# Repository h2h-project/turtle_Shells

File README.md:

# The Hope Turtle Shell
### Our Open Source Printed Circuit Board for the Turtle Control Bottle

The Human2Human project aims to bring hope and humanity to the most hurting and isolated places on the planet — in a way that doesn't trouble the health and happiness of animals, fish and other our fellow creatures. To do so, we've developed the hope turtle: a non-capital, open-source, autonomous marine vehicle that embodies Earthen principles. This repository holds the designs for our "Turtle Shell" printed circuit board.  This is the PCB that holds of microprocessor, sensors and circuits to run our TurtleOS (https://github.com/h2h-project/turtleOS) navigation platform.  

Our vision is to create a simple and inexpensive PCB that anyone anywhere, keen to build a turtle, can put together themselves and set to sail for under 100$ using local and organic materials as much as possible.

## Philosophy

The design of our Turtle Shell PCB is shared under a CERN Open Hardware Licence Version 2 - Strongly Reciprocal.  While our CERN-OHL-S license does not legally restrict military use, we ask that anyone building on this work honor the spirit it was created in — this design exists to bring aid to isolated and vulnerable communities, not for weapons or warfare.  That's the same principle behind releasing this repository at all: any group doing resonant human/ecological work — coastal monitoring, disaster response, ocean research, humanitarian delivery — should be able to take this board, understand exactly how and why it's built the way it is, and carry it further without waiting on us or paying anyone for the privilege.

The Turtle Shell is designed from the ground up to be assembled by hand, by people who have never assembled a circuit board before. Every component on it is through-hole — there is no surface-mount soldering, no solder paste, no reflow oven, nothing that requires equipment beyond a basic iron and a steady hand. Sensors connect via inexpensive, widely-available modules and JST cables rather than being permanently fixed to the board, which keeps the parts list cheap, keeps a broken sensor a five-minute swap rather than a rework job, and keeps the barrier to building one of these low enough that a volunteer, a partner workshop, or a local maker space anywhere in the world can put one together. 

## The PCB

The current version of the Turtle Shell (v2.4) is a compact, two-layer, 70×37mm control board built around the Seeed Studio XIAO ESP32-S3.  While you don't necessarily need a Xiao ESP32-S3 to run turtle (turtleOS v2.3 has a hardware abstraction layer that supports only microprocessors), we've decided to focus our PCB development on this MP after extensively testing various alternatives.   While the Xiao ESP32-S3 is not nearly as equipped and robust as navigation specific boards, it resonates fully with our principles of open source and low-cost decentralized replicability.  The Xiao is also is a fraction of the cost-- which is crucial to our larger project goal of keeping turtle creation cost at under 100$.

The loaded turtle Shell essentially runs TurtleOS and coordinates everything the vessel does. It exposes seven generic 2.00mm JST sensor ports plus a dedicated GPS port, so the same board can carry whatever mix of instruments a given voyage needs — a magnetic angle encoder for rudder position, a combined accelerometer/gyroscope/compass/barometer for heading and weather, a current and voltage monitor for tracking the power budget, a temperature and humidity sensor to watch over the sealed enclosure's health — alongside dedicated sockets for a display and a real-time clock, breakout headers for the microcontroller's full pinout, and a servo connector kept deliberately isolated from the board's own power traces. It's a small board asked to do a lot, and every connector on it exists because a real sensor needed a reliable, correctly-oriented place to plug in.

Here's a quick list of our core components for our v.24 turtle shell:

| Component | Function | Interface | Approx. Cost (USD) |
|---|---|---|---|
| Seeed XIAO ESP32-S3 | Main microcontroller, runs TurtleOS | — | ~$7.50 |
| Xiao GPS module | Position & UTC time | UART, GPS1 port | ~$7 |
| GY-87 10DOF (MPU6050 + HMC5883L/QMC5883 + BMP180) | Heading, attitude, barometric pressure | I²C, SEN port | ~$7 |
| AS5600 | Rudder/servo angle sensing | I²C, SEN port | ~$1.50 |
| INA219 (GY-219) | Battery current, voltage & power monitoring | I²C, SEN port | ~$2 |
| AHT20 | Enclosure temperature & humidity | I²C, SEN port | ~$2.50 |
| 1.3" OLED (SH1106) | Status display | I²C, SCREEN1 socket | ~$4.50 |
| DS3231 RTC (5-pin) | Spoof-resistant, GPS-independent timekeeping | I²C, RTC1 header | ~$3.50 |
| JST↔Dupont cables (×6, mixed lengths) | Connect modules to SEN ports | — | ~$3 |
| **Subtotal** | | | **~$38** |

You can see an indepth breakdown of the Turtle hardware stack here:
https://github.com/h2h-project/turtleOS/blob/main/hardware_stack.md

## Where We're Headed

As of August 2026 we're in full development, printing and prototyping mode-- so things are evolving fast!  

The next revision is aimed at making the board more self-contained and more reliable at sea, without giving up the simplicity that makes it buildable by hand. We're working out how to bring battery power directly onto the board — using spring-loaded contacts to reach the microcontroller module's own charging circuit rather than routing through a less efficient path — alongside dedicated, correctly-keyed sockets for the current sensor and the inertial measurement unit, and a permanent home for the solar charging circuit, so fewer loose modules and wires are rattling around inside a hull that will spend weeks rolling in ocean swell. None of this is finished, and some of it may not survive contact with the next prototype — but the goal stays the same: a board that's a little more finished each time, still cheap, still imminently buildable, and still something anyone resonating with this repository and our human2human project can pick up and carry forward.

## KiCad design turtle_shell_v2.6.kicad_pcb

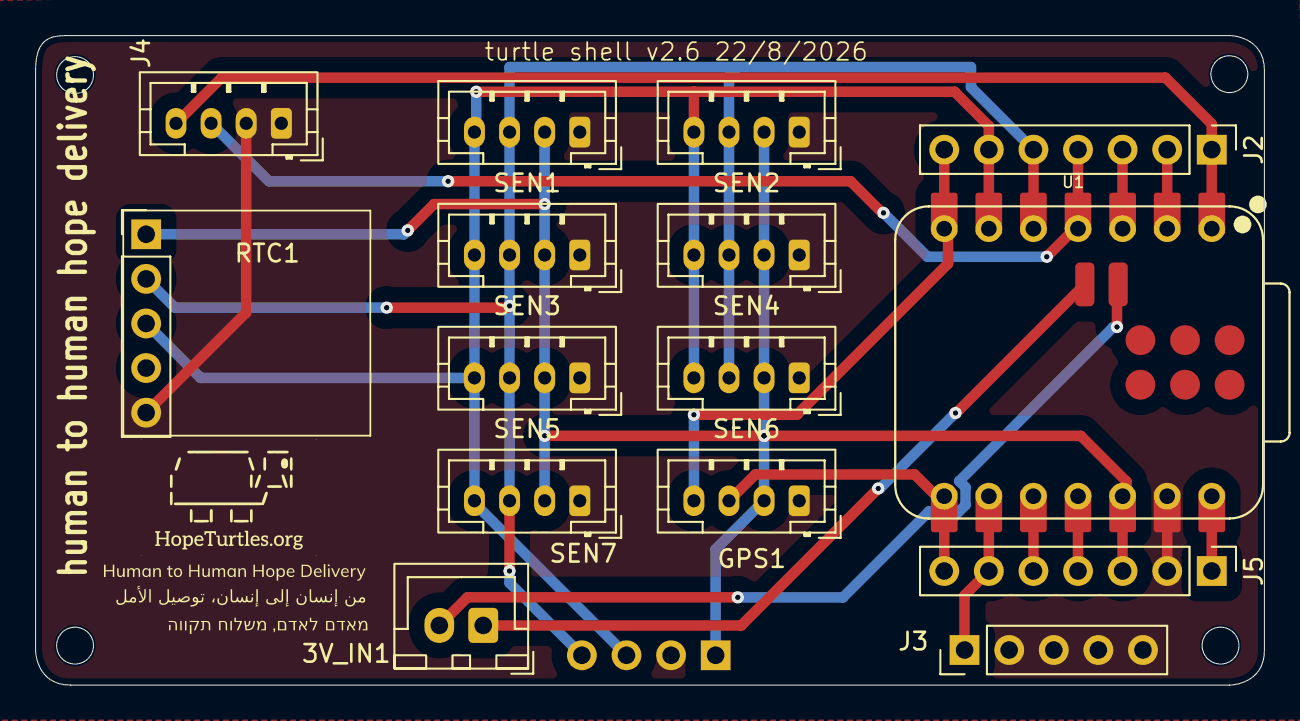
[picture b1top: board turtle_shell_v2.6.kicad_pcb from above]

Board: 2 copper layers, 70.0 x 37.0 mm, 20 parts (1 on the bottom side), 16 nets.

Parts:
3V_IN1: 3v_in; JST_XH_B2B-XH-A_1x02_P2.50mm_Vertical
GPS1: gps; JST_PH_B4B-PH-K_1x04_P2.00mm_Vertical
H1, H2, H3, H4: MountingHole; MountingHole_2.1mm
J2, J5: 7 pin header; PinHeader_1x07_P2.54mm_Vertical
J3: servo gnd; PinHeader_1x05_P2.54mm_Vertical
J4: btn/led_con; JST_PH_B4B-PH-K_1x04_P2.00mm_Vertical
RTC1: RTC; PinHeader_1x05_P2.54mm_Vertical
SCREEN1: sensor; PinSocket_1x04_P2.54mm_Vertical
SEN1, SEN2, SEN3, SEN4, SEN5, SEN6, SEN7: sensor; JST_PH_B4B-PH-K_1x04_P2.00mm_Vertical
U1: XIAO-ESP32-C3-SMD; XIAO-ESP32-C3-DIP-SMD

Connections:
GND: GPS1.1, J3.2, J3.3, J3.4, J3.5, J4.1, J4.2, J5.2, RTC1.5, SCREEN1.2, SEN1.1, SEN2.1, SEN3.1, SEN4.1, SEN5.1, SEN6.1, SEN7.1, U1.13 (GND)
unnamed: 3V_IN1.1, U1.21 (VBAT)
unnamed: 3V_IN1.2, U1.22 (GND)
unnamed: GPS1.2, J5.3, RTC1.1, SCREEN1.1, SEN1.2, SEN2.2, SEN3.2, SEN4.2, SEN5.2, SEN6.2, SEN7.2, U1.12 (3V3_OUT)
unnamed: GPS1.3, J5.7, U1.8 (D7)
unnamed: GPS1.4, J2.7, U1.7 (D6)
unnamed: J2.1, J4.4, U1.1 (D0)
unnamed: J2.2, U1.2 (D1)
unnamed: J2.3, U1.3 (D2)
unnamed: J2.4, J4.3, U1.4 (D3)
unnamed: J2.5, RTC1.2, SCREEN1.4, SEN1.3, SEN2.3, SEN3.3, SEN4.3, SEN5.3, SEN6.3, SEN7.3, U1.5 (D4)
unnamed: J2.6, RTC1.3, SCREEN1.3, SEN1.4, SEN2.4, SEN3.4, SEN4.4, SEN5.4, SEN6.4, SEN7.4, U1.6 (D5)
unnamed: J3.1, J5.6, U1.9 (D8)
unnamed: J5.1, U1.14 (VBUS)
unnamed: J5.4, U1.11 (D10)
unnamed: J5.5, U1.10 (D9/BOOT)
